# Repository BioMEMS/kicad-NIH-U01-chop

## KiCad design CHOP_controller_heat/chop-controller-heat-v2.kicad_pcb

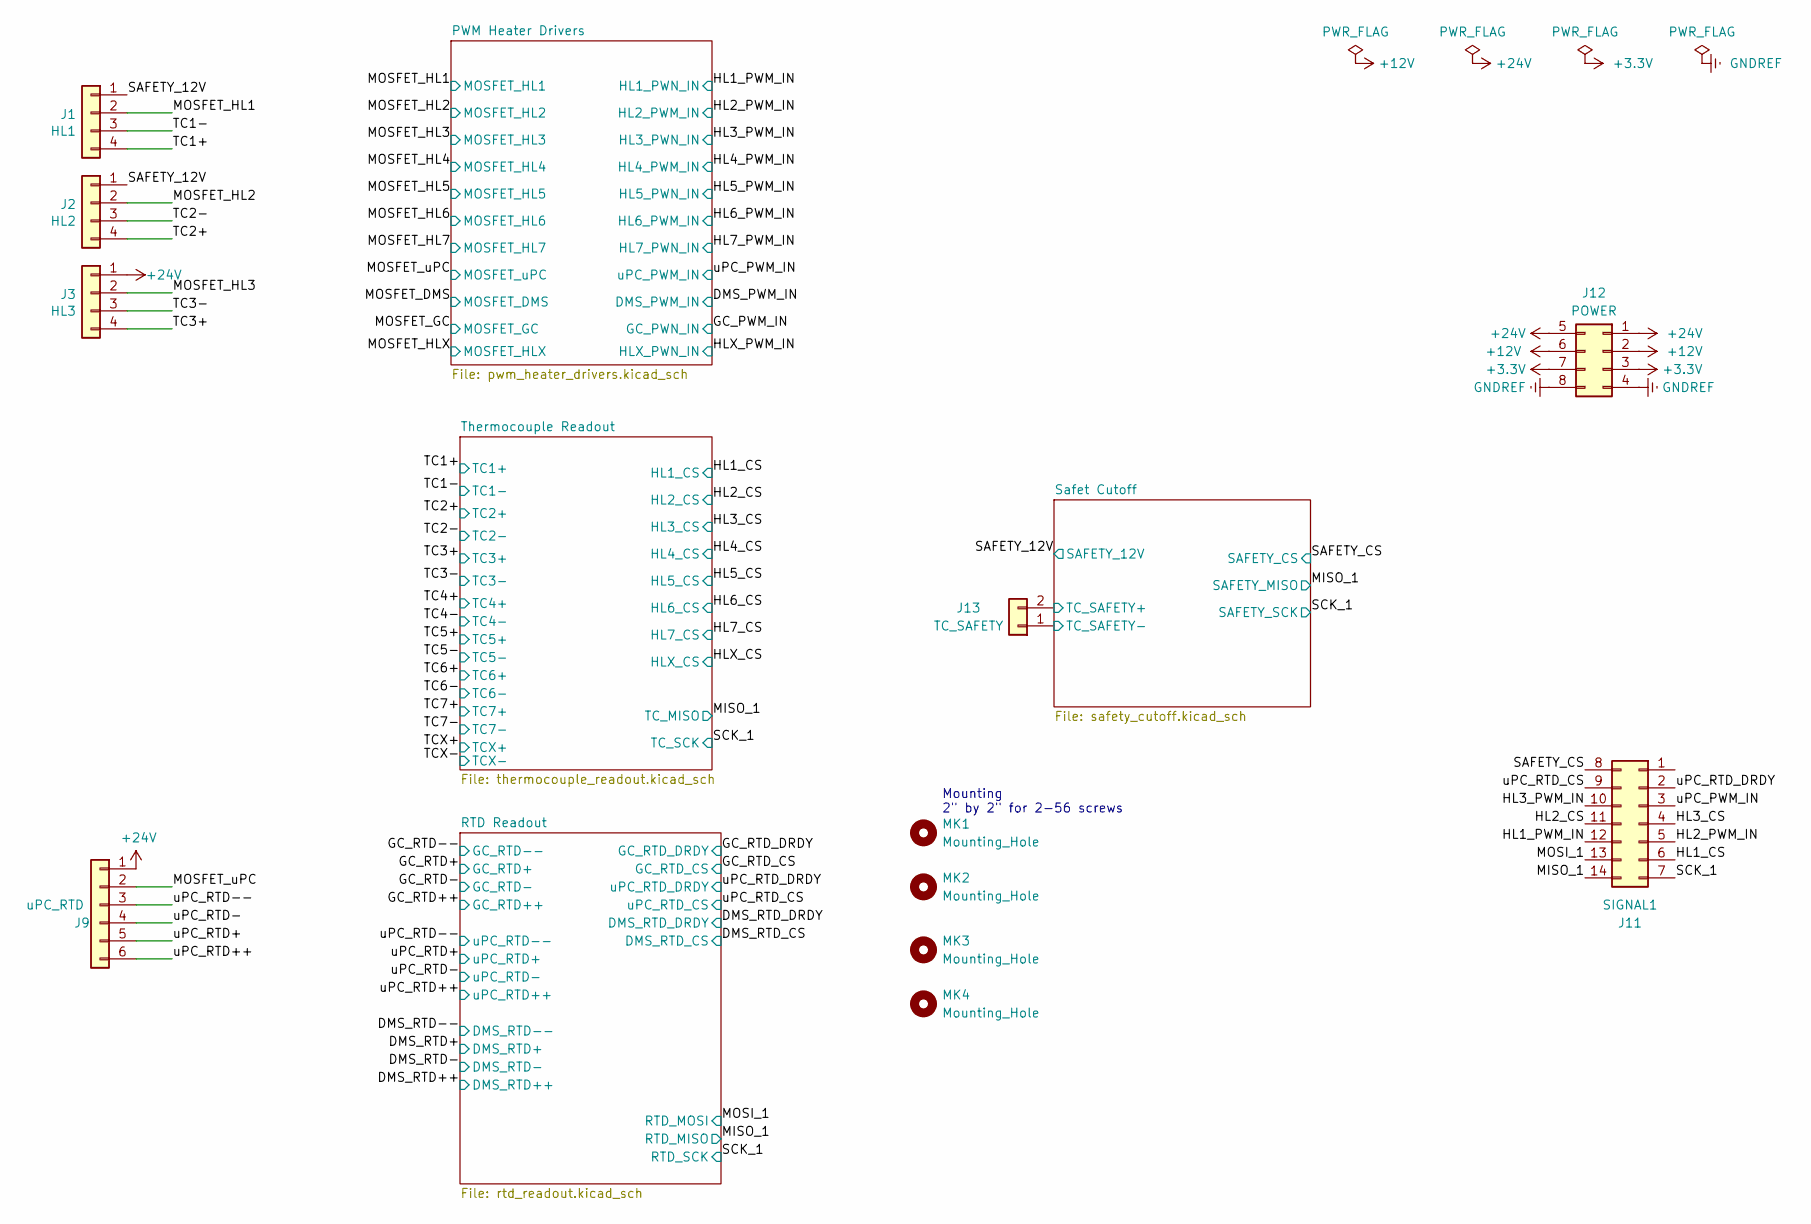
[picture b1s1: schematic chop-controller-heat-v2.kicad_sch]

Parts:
J1: HL1; Molex_SL_171975-0004_1x04_P2.54mm_Horizontal
J2: HL2; Molex_SL_171975-0004_1x04_P2.54mm_Horizontal
J3: HL3; Molex_SL_171975-0004_1x04_P2.54mm_Horizontal
J9: uPC_RTD; Molex_SL_171975-0006_1x06_P2.54mm_Horizontal
J11: SIGNAL1; Molex_Micro-Fit_3.0_43045-1400_2x07_P3.00mm_Horizontal
J12: POWER; Molex_Micro-Fit_3.0_43045-0800_2x04_P3.00mm_Horizontal
J13: TC_SAFETY; Molex_SL_171975-0002_1x02_P2.54mm_Horizontal
MK1, MK2, MK3, MK4: Mounting_Hole; MountingHole_3.2mm_M3

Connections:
+3.3V: J12.3, J12.7; also elsewhere on the board
+12V: J12.2, J12.6; also elsewhere on the board
+24V: J3.1, J9.1, J12.1, J12.5
/HL1_CS: J11.6; also elsewhere on the board
/HL1_PWM_IN: J11.12; also elsewhere on the board
/HL2_CS: J11.11; also elsewhere on the board
/HL2_PWM_IN: J11.5; also elsewhere on the board
/HL3_CS: J11.4; also elsewhere on the board
/HL3_PWM_IN: J11.10; also elsewhere on the board
/MISO_1: J11.14; also elsewhere on the board
/MOSFET_HL1: J1.2; also elsewhere on the board
/MOSFET_HL2: J2.2; also elsewhere on the board
/MOSFET_HL3: J3.2; also elsewhere on the board
/MOSFET_uPC: J9.2; also elsewhere on the board
/MOSI_1: J11.13; also elsewhere on the board
/SAFETY_12V: J1.1, J2.1; also elsewhere on the board
/SAFETY_CS: J11.8; also elsewhere on the board
/SCK_1: J11.7; also elsewhere on the board
/Safet Cutoff/TC_SAFETY+: J13.2; also elsewhere on the board
/Safet Cutoff/TC_SAFETY-: J13.1; also elsewhere on the board
/TC1+: J1.4; also elsewhere on the board
/TC1-: J1.3; also elsewhere on the board
/TC2+: J2.4; also elsewhere on the board
/TC2-: J2.3; also elsewhere on the board
/TC3+: J3.4; also elsewhere on the board
/TC3-: J3.3; also elsewhere on the board
/uPC_PWM_IN: J11.3; also elsewhere on the board
/uPC_RTD+: J9.5; also elsewhere on the board
/uPC_RTD++: J9.6; also elsewhere on the board
/uPC_RTD-: J9.4; also elsewhere on the board
/uPC_RTD--: J9.3; also elsewhere on the board
/uPC_RTD_CS: J11.9; also elsewhere on the board
/uPC_RTD_DRDY: J11.2; also elsewhere on the board
GNDREF: J12.4, J12.8; also elsewhere on the board

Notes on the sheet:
Mounting 2" by 2" for 2-56 screws

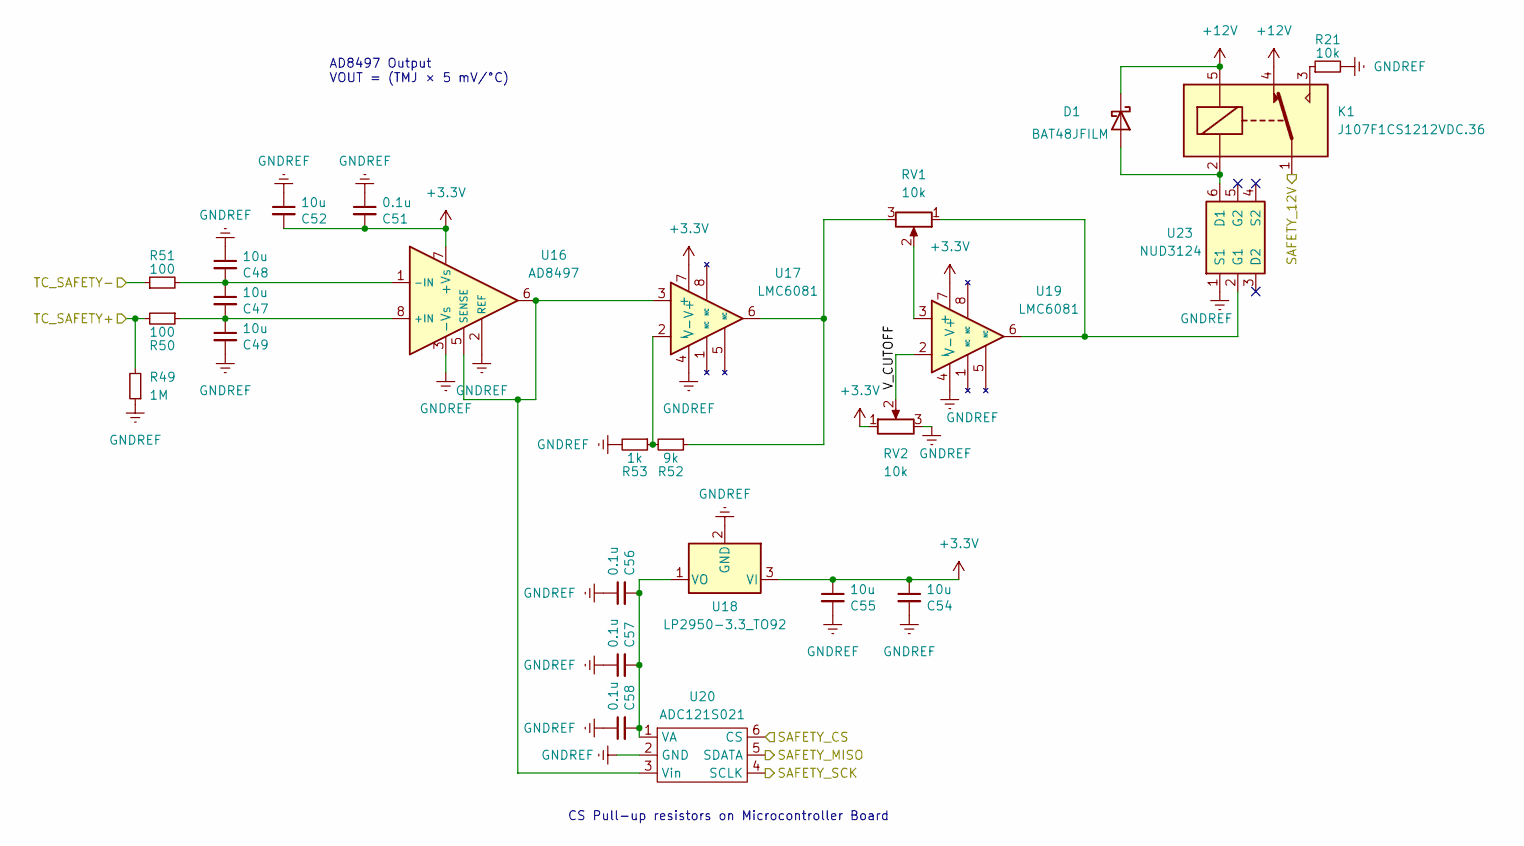
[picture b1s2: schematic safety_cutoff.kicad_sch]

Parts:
C47, C48, C49, C52, C54, C55: 10u; C_0603_1608Metric_HandSolder
C51, C56, C57, C58: 0.1u; C_0603_1608Metric_HandSolder
D1: BAT48JFILM; D_SOD-323
K1: J107F1CS1212VDC.36; Relay_SPDT_SANYOU_SRD_Series_Form_C
R21: 10k; R_0603_1608Metric
R49: 1M; R_0603_1608Metric
R50, R51: 100; R_0603_1608Metric
R52: 9k; R_0603_1608Metric
R53: 1k; R_0603_1608Metric
RV1, RV2: 10k; Potentiometer_Bourns_3296W_Vertical
U16: AD8497; MSOP-8_3x3mm_P0.65mm
U17, U19: LMC6081; SOIC-8_3.9x4.9mm_P1.27mm
U18: LP2950-3.3_TO92; TO-92_Inline
U20: ADC121S021; SOT-23-6
U23: NUD3124; SOT-23-6

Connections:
+3.3V: C51.2, C52.2, C54.1, C55.1, RV2.1, U16.7 (+Vs), U17.7 (V+), U18.3 (VI), U19.7 (V+); also elsewhere on the board
+12V: D1.1 (K), K1.4, K1.5; also elsewhere on the board
/MISO_1: U20.5 (SDATA); also elsewhere on the board
/SAFETY_12V: K1.1; also elsewhere on the board
/SAFETY_CS: U20.6 (CS); also elsewhere on the board
/SCK_1: U20.4 (SCLK); also elsewhere on the board
/Safet Cutoff/TC_SAFETY+: R49.2, R50.2; also elsewhere on the board
/Safet Cutoff/TC_SAFETY-: R51.1; also elsewhere on the board
/Safet Cutoff/V_CUTOFF: RV2.2, U19.2 (-)
GNDREF: C48.1, C49.2, C51.1, C52.1, C54.2, C55.2, C56.1, C57.1, C58.1, R21.2, R49.1, R53.2, RV2.3, U16.2 (REF), U16.3 (-Vs), U17.4 (V-), U18.2 (GND), U19.4 (V-), U20.2 (GND), U23.1 (S1); also elsewhere on the board
unnamed: D1.2 (A), K1.2, U23.6 (D1)
unnamed: K1.3, R21.1
unnamed: R52.1, RV1.3, U17.6
unnamed: C47.2, C49.1, R50.1, U16.8 (+IN)
unnamed: C47.1, C48.2, R51.2, U16.1 (-IN)
unnamed: U16.5 (SENSE), U16.6, U17.3 (+), U20.3 (Vin)
unnamed: R52.2, R53.1, U17.2 (-)
unnamed: C56.2, C57.2, C58.2, U18.1 (VO), U20.1 (VA)
unnamed: RV1.2, U19.3 (+)
unnamed: RV1.1, U19.6, U23.2 (G1)

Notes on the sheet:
AD8497 Output VOUT = (TMJ × 5 mV/°C)
CS Pull-up resistors on Microcontroller Board

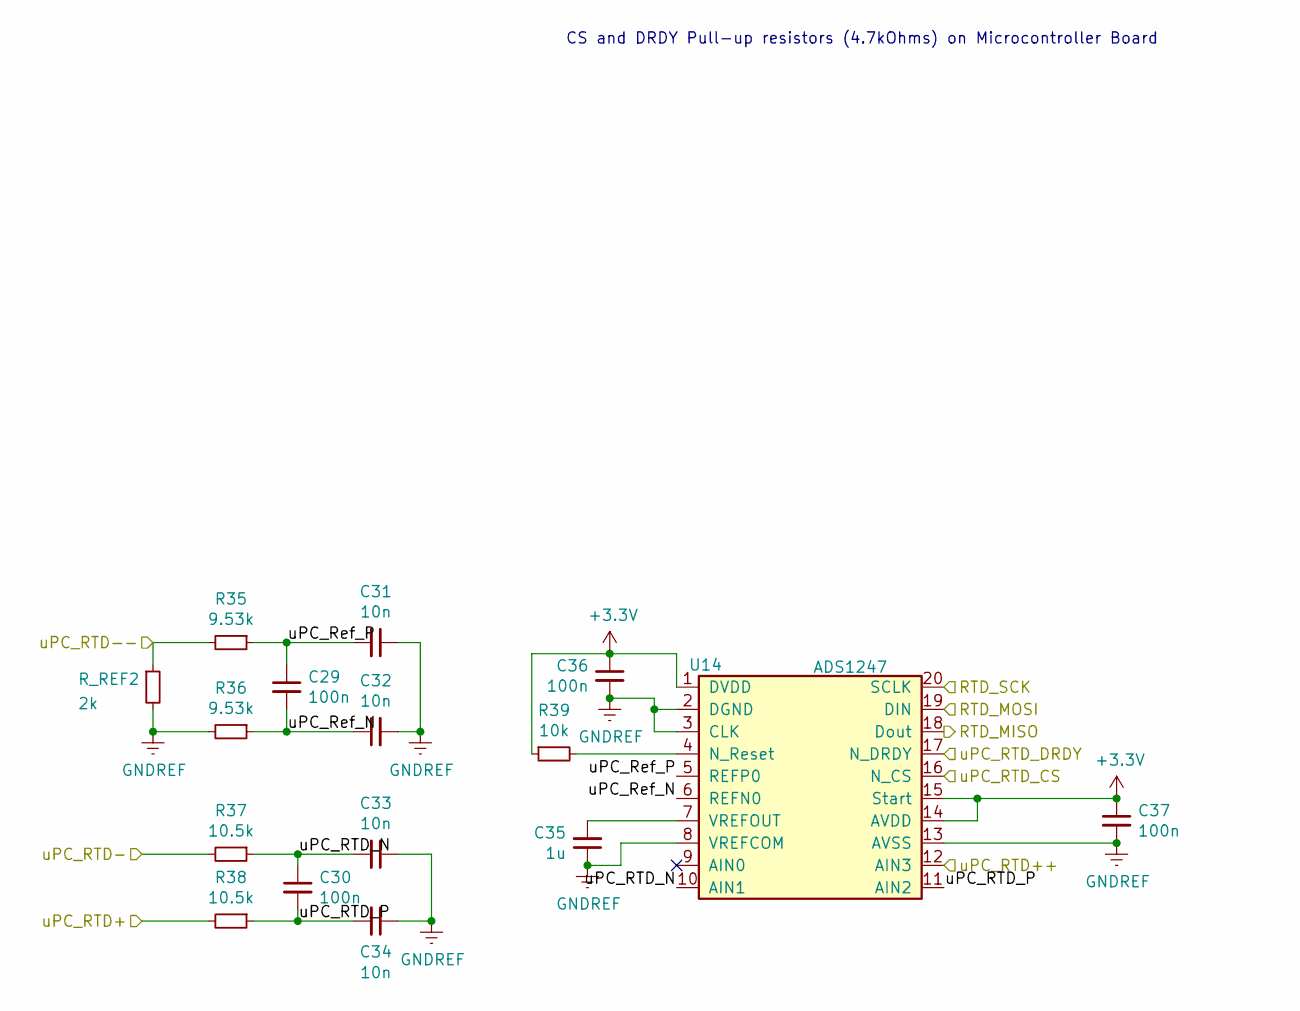
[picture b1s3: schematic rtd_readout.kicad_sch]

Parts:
C29, C30, C36, C37: 100n; C_0603_1608Metric_HandSolder
C31, C32, C33, C34: 10n; C_0603_1608Metric_HandSolder
C35: 1u; C_0603_1608Metric_HandSolder
R35, R36: 9.53k; R_0603_1608Metric
R37, R38: 10.5k; R_0603_1608Metric
R39: 10k; R_0603_1608Metric
R_REF2: 2k; R_0603_1608Metric
U14: ADS1247; TSSOP-20_4.4x6.5mm_P0.65mm; MPN ADS1247IPW

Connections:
+3.3V: C36.1, C37.1, R39.1, U14.1 (DVDD), U14.14 (AVDD), U14.15 (Start); also elsewhere on the board
/MISO_1: U14.18 (Dout); also elsewhere on the board
/MOSI_1: U14.19 (DIN); also elsewhere on the board
/RTD Readout/uPC_RTD_N: C30.1, C33.2, R37.1, U14.10 (AIN1)
/RTD Readout/uPC_RTD_P: C30.2, C34.2, R38.1, U14.11 (AIN2)
/RTD Readout/uPC_Ref_N: C29.2, C32.1, R36.1, U14.6 (REFN0)
/RTD Readout/uPC_Ref_P: C29.1, C31.2, R35.1, U14.5 (REFP0)
/SCK_1: U14.20 (SCLK); also elsewhere on the board
/uPC_RTD+: R38.2; also elsewhere on the board
/uPC_RTD++: U14.12 (AIN3); also elsewhere on the board
/uPC_RTD-: R37.2; also elsewhere on the board
/uPC_RTD--: R35.2, R_REF2.1; also elsewhere on the board
/uPC_RTD_CS: U14.16 (N_CS); also elsewhere on the board
/uPC_RTD_DRDY: U14.17 (N_DRDY); also elsewhere on the board
GNDREF: C31.1, C32.2, C33.1, C34.1, C35.1, C36.2, C37.2, R36.2, R_REF2.2, U14.2 (DGND), U14.3 (CLK), U14.8 (VREFCOM), U14.13 (AVSS); also elsewhere on the board
unnamed: R39.2, U14.4 (N_Reset)
unnamed: C35.2, U14.7 (VREFOUT)

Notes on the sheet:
CS and DRDY Pull-up resistors (4.7kOhms) on Microcontroller Board

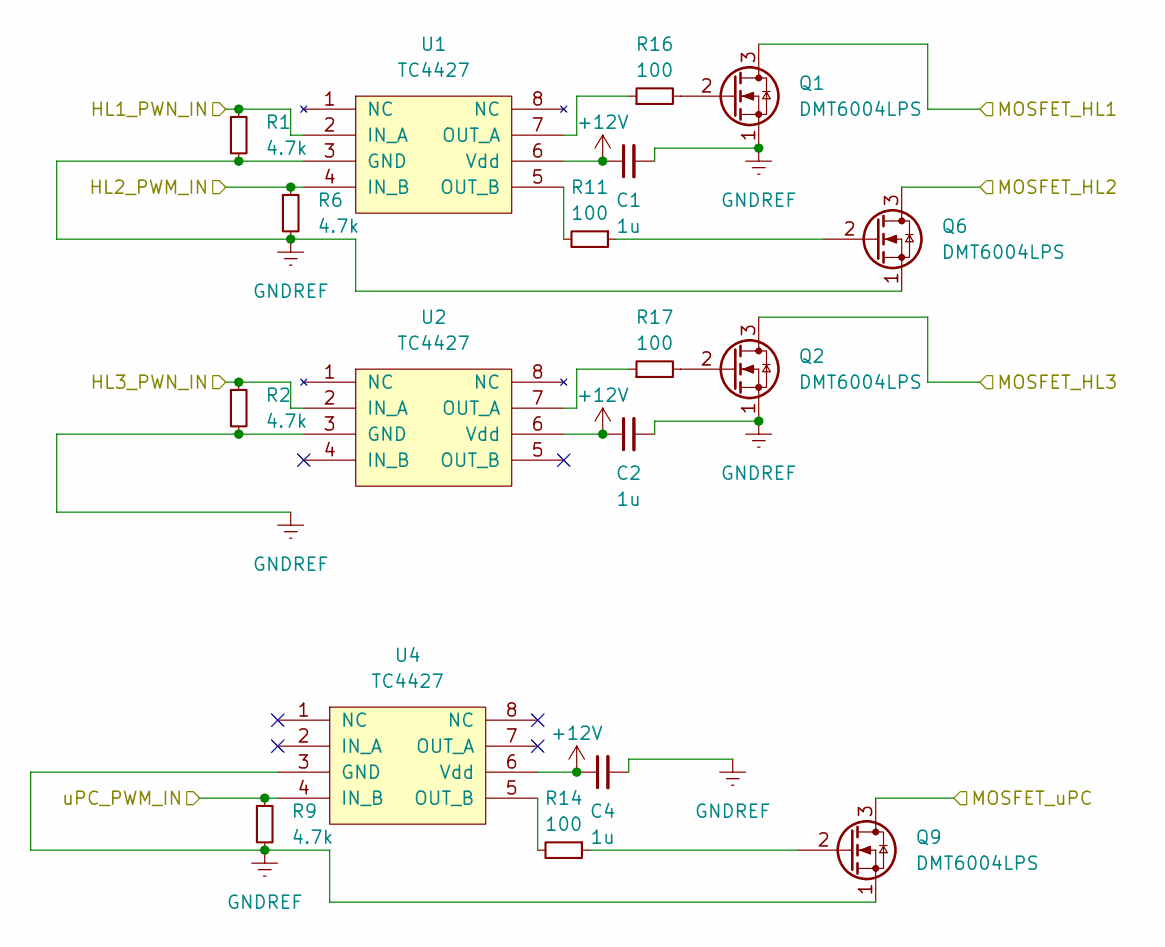
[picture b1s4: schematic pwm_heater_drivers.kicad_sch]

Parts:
C1, C2, C4: 1u; C_0603_1608Metric_HandSolder
Q1, Q2, Q6, Q9: DMT6004LPS; PowerDI5060-8
R1, R2, R6, R9: 4.7k; R_0603_1608Metric
R11, R14, R16, R17: 100; R_0603_1608Metric
U1, U2, U4: TC4427; MSOP-8_3x3mm_P0.65mm_TI

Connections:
+12V: C1.1, C2.1, C4.1, U1.6 (Vdd), U2.6 (Vdd), U4.6 (Vdd); also elsewhere on the board
/HL1_PWM_IN: R1.1, U1.2 (IN_A); also elsewhere on the board
/HL2_PWM_IN: R6.1, U1.4 (IN_B); also elsewhere on the board
/HL3_PWM_IN: R2.1, U2.2 (IN_A); also elsewhere on the board
/MOSFET_HL1: Q1.3 (D); also elsewhere on the board
/MOSFET_HL2: Q6.3 (D); also elsewhere on the board
/MOSFET_HL3: Q2.3 (D); also elsewhere on the board
/MOSFET_uPC: Q9.3 (D); also elsewhere on the board
/uPC_PWM_IN: R9.1, U4.4 (IN_B); also elsewhere on the board
GNDREF: C1.2, C2.2, C4.2, Q1.1 (S), Q2.1 (S), Q6.1 (S), Q9.1 (S), R1.2, R2.2, R6.2, R9.2, U1.3 (GND), U2.3 (GND), U4.3 (GND); also elsewhere on the board
unnamed: Q1.2 (G), R16.2
unnamed: Q2.2 (G), R17.2
unnamed: Q6.2 (G), R11.1
unnamed: Q9.2 (G), R14.1
unnamed: R16.1, U1.7 (OUT_A)
unnamed: R11.2, U1.5 (OUT_B)
unnamed: R17.1, U2.7 (OUT_A)
unnamed: R14.2, U4.5 (OUT_B)

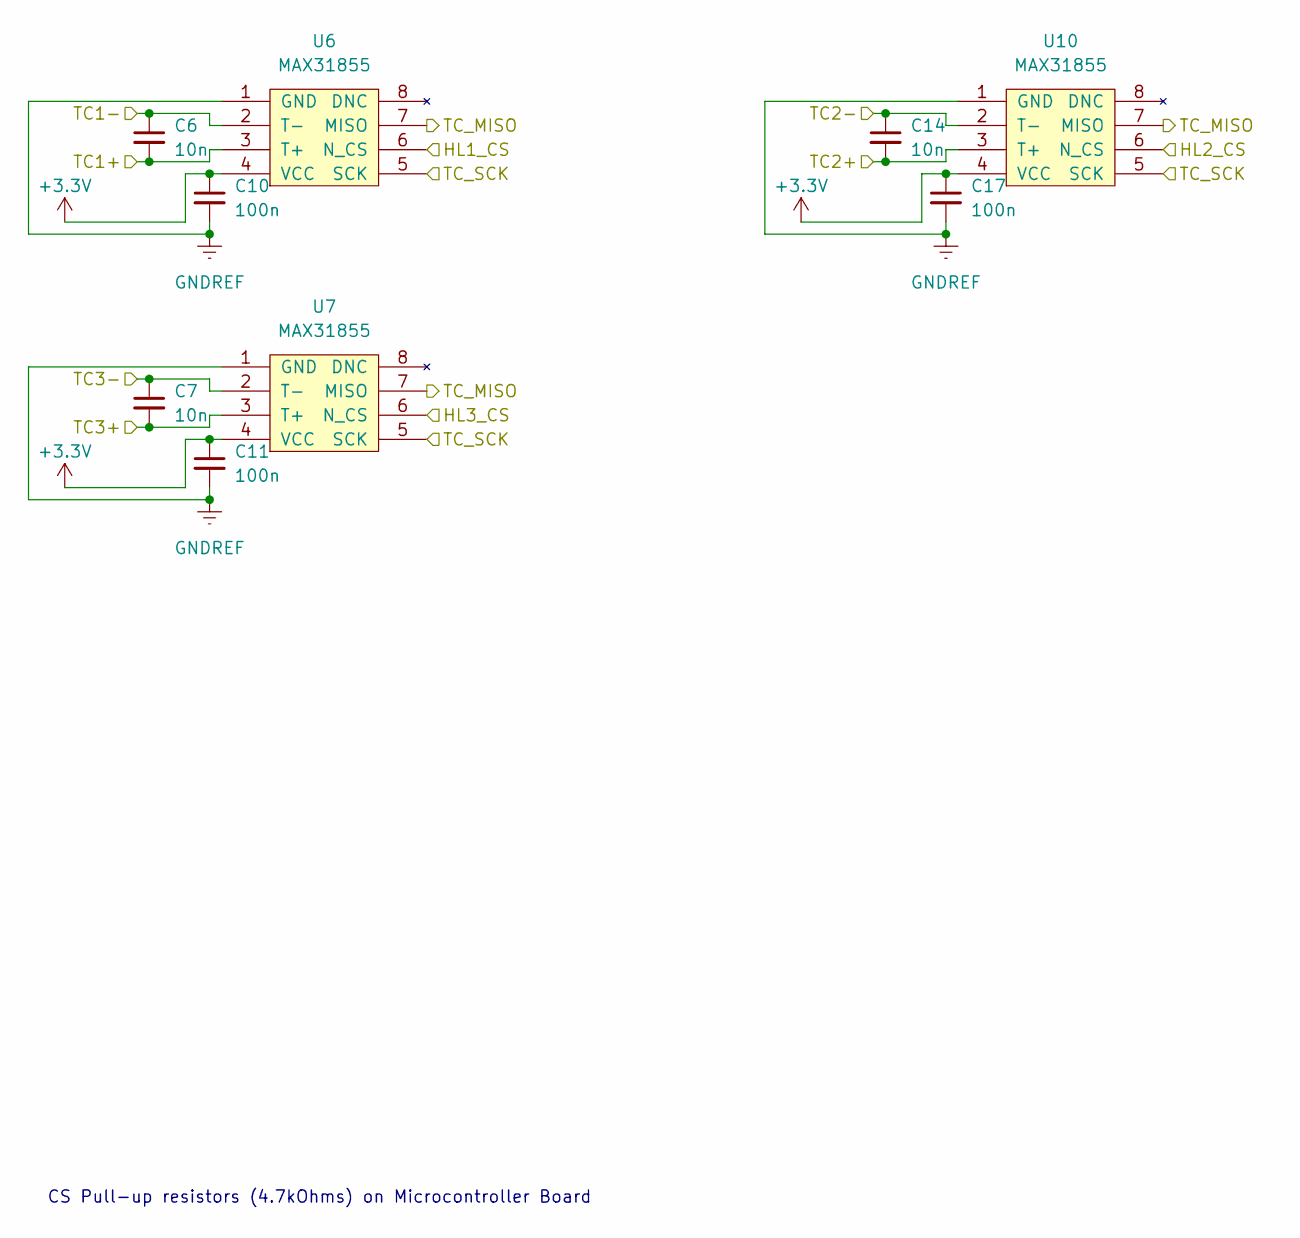
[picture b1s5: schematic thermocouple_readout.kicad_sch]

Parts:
C6, C7, C14: 10n; C_0603_1608Metric_HandSolder
C10, C11, C17: 100n; C_0603_1608Metric_HandSolder
U6, U7, U10: MAX31855; SO-8_Maxim

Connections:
+3.3V: C10.1, C11.1, C17.1, U6.4 (VCC), U7.4 (VCC), U10.4 (VCC); also elsewhere on the board
/HL1_CS: U6.6 (N_CS); also elsewhere on the board
/HL2_CS: U10.6 (N_CS); also elsewhere on the board
/HL3_CS: U7.6 (N_CS); also elsewhere on the board
/MISO_1: U6.7 (MISO), U7.7 (MISO), U10.7 (MISO); also elsewhere on the board
/SCK_1: U6.5 (SCK), U7.5 (SCK), U10.5 (SCK); also elsewhere on the board
/TC1+: C6.2, U6.3 (T+); also elsewhere on the board
/TC1-: C6.1, U6.2 (T-); also elsewhere on the board
/TC2+: C14.2, U10.3 (T+); also elsewhere on the board
/TC2-: C14.1, U10.2 (T-); also elsewhere on the board
/TC3+: C7.2, U7.3 (T+); also elsewhere on the board
/TC3-: C7.1, U7.2 (T-); also elsewhere on the board
GNDREF: C10.2, C11.2, C17.2, U6.1 (GND), U7.1 (GND), U10.1 (GND); also elsewhere on the board

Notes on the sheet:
CS Pull-up resistors (4.7kOhms) on Microcontroller Board

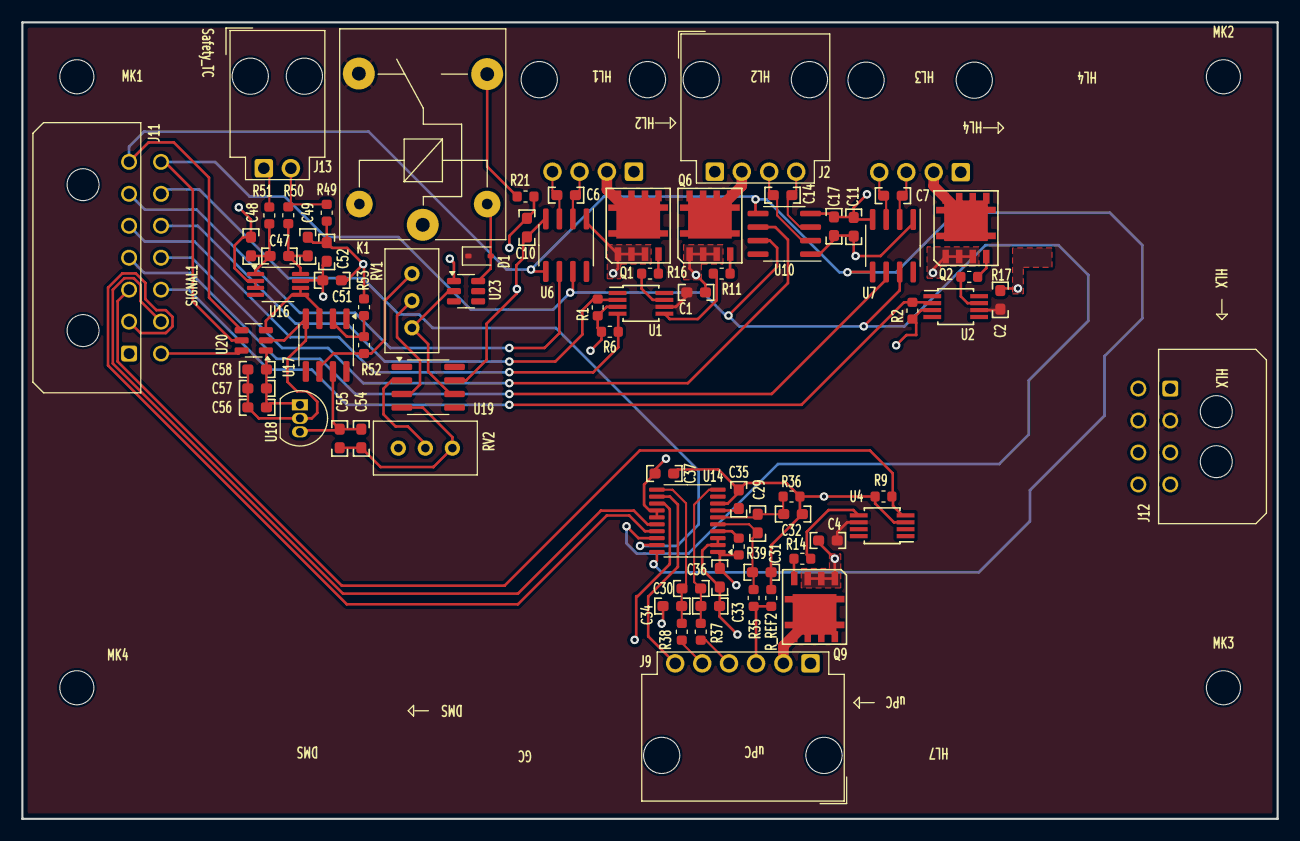
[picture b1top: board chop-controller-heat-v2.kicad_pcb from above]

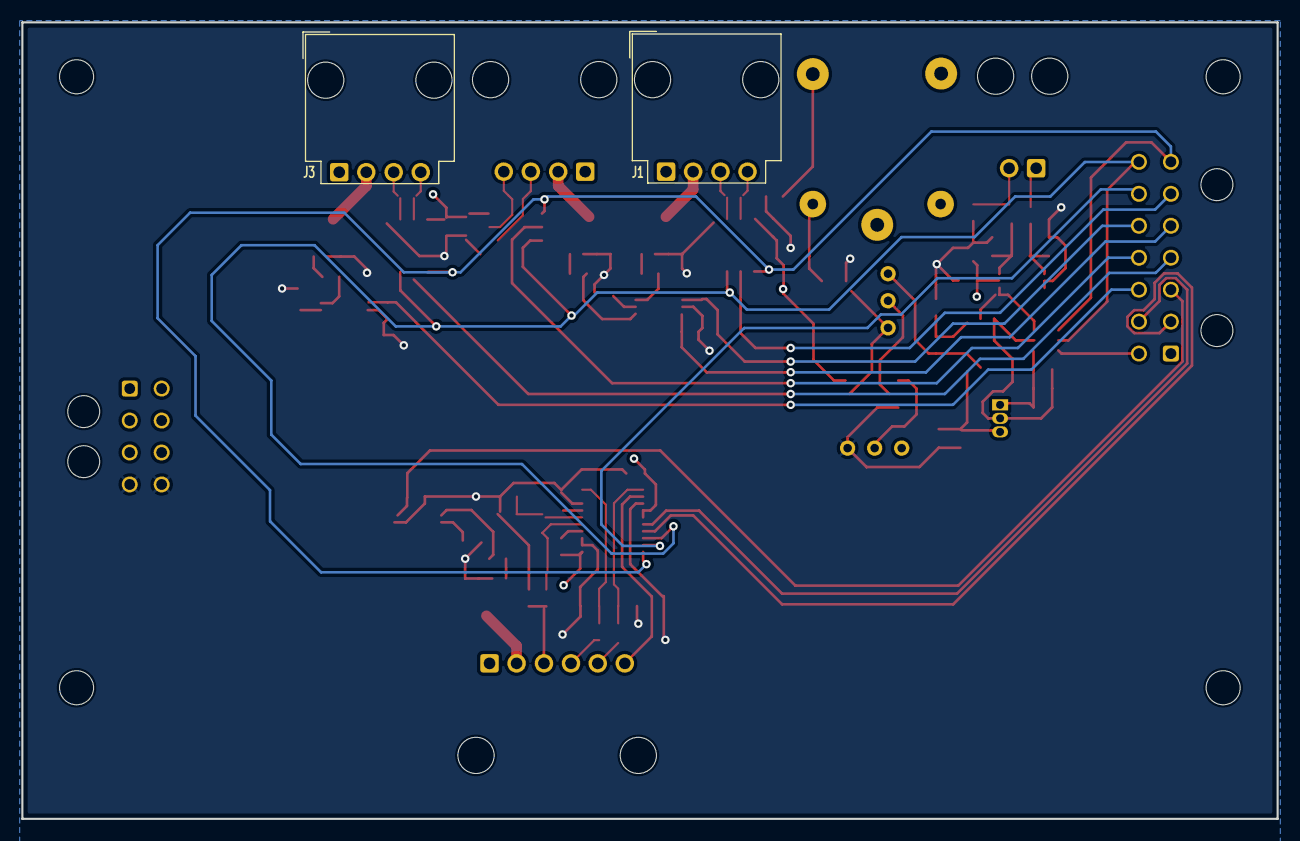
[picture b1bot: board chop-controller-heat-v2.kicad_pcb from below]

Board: 4 copper layers, 117.9 x 74.8 mm, 80 parts (2 on the bottom side), 59 nets.

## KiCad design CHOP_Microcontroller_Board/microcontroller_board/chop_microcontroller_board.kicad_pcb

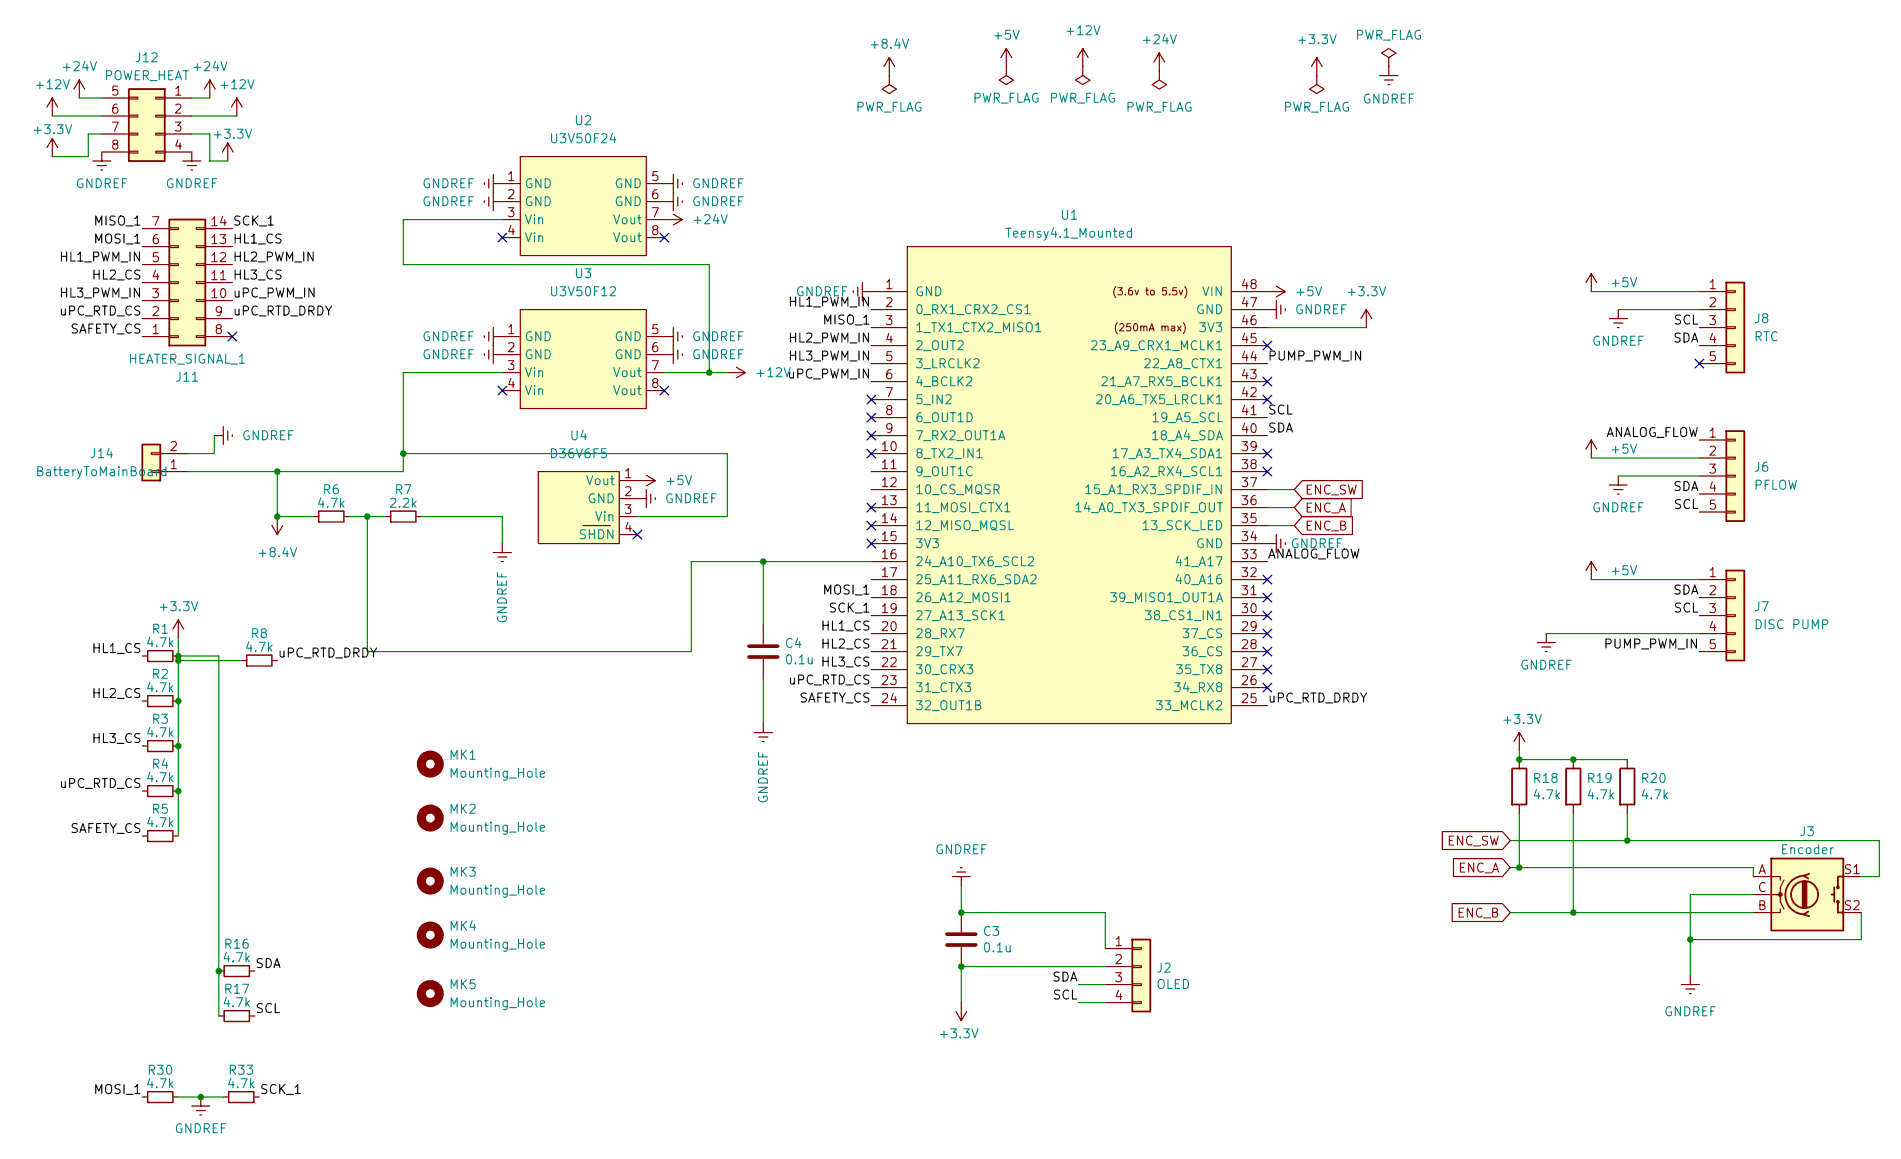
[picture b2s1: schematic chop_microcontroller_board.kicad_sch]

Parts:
C3, C4: 0.1u; C_0603_1608Metric_HandSolder
J2: OLED; 128x64OLED
J3: Encoder; RotaryEncoder_Alps_EC12E-Switch_Vertical_H20mm
J6: PFLOW; Molex_Micro-Fit_3.0_43650-0500_1x05_P3.00mm_Horizontal
J7: DISC PUMP; Molex_Micro-Fit_3.0_43650-0500_1x05_P3.00mm_Horizontal
J8: RTC; PinHeader_1x05_P2.54mm_Vertical
J11: HEATER_SIGNAL_1; Molex_Micro-Fit_3.0_43045-1400_2x07_P3.00mm_Horizontal
J12: POWER_HEAT; Molex_Micro-Fit_3.0_43045-0800_2x04_P3.00mm_Horizontal
J14: BatteryToMainBoard; JST_PH_S2B-PH-K_1x02_P2.00mm_Horizontal
MK1, MK2, MK3, MK4, MK5: Mounting_Hole; MountingHole_3.2mm_M3
R1, R2, R3, R4, R5, R6, R8, R16, R17, R30, R33: 4.7k; R_0603_1608Metric
R7: 2.2k; R_0603_1608Metric
R18, R19, R20: 4.7k; R_0805_2012Metric
U1: Teensy4.1_Mounted; Teensy41_Mounted
U2: U3V50F24; U3V50F24StepUpReg
U3: U3V50F12; U3V50F12StepUpReg
U4: D36V6F5; PinHeader_1x04_P2.54mm_Vertical

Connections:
+3.3V: C3.2, J2.2, J12.3, J12.7, R1.2, R2.2, R3.2, R4.2, R5.2, R8.1, R16.2, R17.2, R18.1, R19.1, R20.1, U1.46 (3V3)
+5V: J6.2, J7.1, J8.1, U1.48 (VIN), U4.1 (Vout)
+8.4V: J14.1, R6.1, U3.3 (Vin), U4.3 (Vin)
+12V: J12.2, J12.6, U2.3 (Vin), U3.7 (Vout)
+24V: J12.1, J12.5, U2.7 (Vout)
/ANALOG_FLOW: J6.1, U1.33 (41_A17)
/HL1_CS: J11.13, R1.1, U1.20 (28_RX7)
/HL1_PWM_IN: J11.5, U1.2 (0_RX1_CRX2_CS1)
/HL2_CS: J11.4, R2.1, U1.21 (29_TX7)
/HL2_PWM_IN: J11.12, U1.4 (2_OUT2)
/HL3_CS: J11.11, R3.1, U1.22 (30_CRX3)
/HL3_PWM_IN: J11.3, U1.5 (3_LRCLK2)
/MISO_1: J11.7, U1.3 (1_TX1_CTX2_MISO1)
/MOSI_1: J11.6, R30.1, U1.18 (26_A12_MOSI1)
/PUMP_PWM_IN: J7.5, U1.44 (22_A8_CTX1)
/SAFETY_CS: J11.1, R5.1, U1.24 (32_OUT1B)
/SCK_1: J11.14, R33.1, U1.19 (27_A13_SCK1)
/SCL: J2.4, J6.5, J7.3, J8.3, R17.1, U1.41 (19_A5_SCL)
/SDA: J2.3, J6.4, J7.2, J8.4, R16.1, U1.40 (18_A4_SDA)
/uPC_PWM_IN: J11.10, U1.6 (4_BCLK2)
/uPC_RTD_CS: J11.2, R4.1, U1.23 (31_CTX3)
/uPC_RTD_DRDY: J11.9, R8.2, U1.25 (33_MCLK2)
ENC_A: J3.A, R18.2, U1.36 (14_A0_TX3_SPDIF_OUT)
ENC_B: J3.B, R19.2, U1.35 (13_SCK_LED)
ENC_SW: J3.S1, R20.2, U1.37 (15_A1_RX3_SPDIF_IN)
GNDREF: C3.1, C4.2, J2.1, J3.C, J3.S2, J6.3, J7.4, J8.2, J12.4, J12.8, J14.2, R7.2, R30.2, R33.2, U1.1 (GND), U1.34 (GND), U1.47 (GND), U2.1 (GND), U2.2 (GND), U2.5 (GND), U2.6 (GND), U3.1 (GND), U3.2 (GND), U3.5 (GND), U3.6 (GND), U4.2 (GND)
unnamed: C4.1, R6.2, R7.1, U1.16 (24_A10_TX6_SCL2)

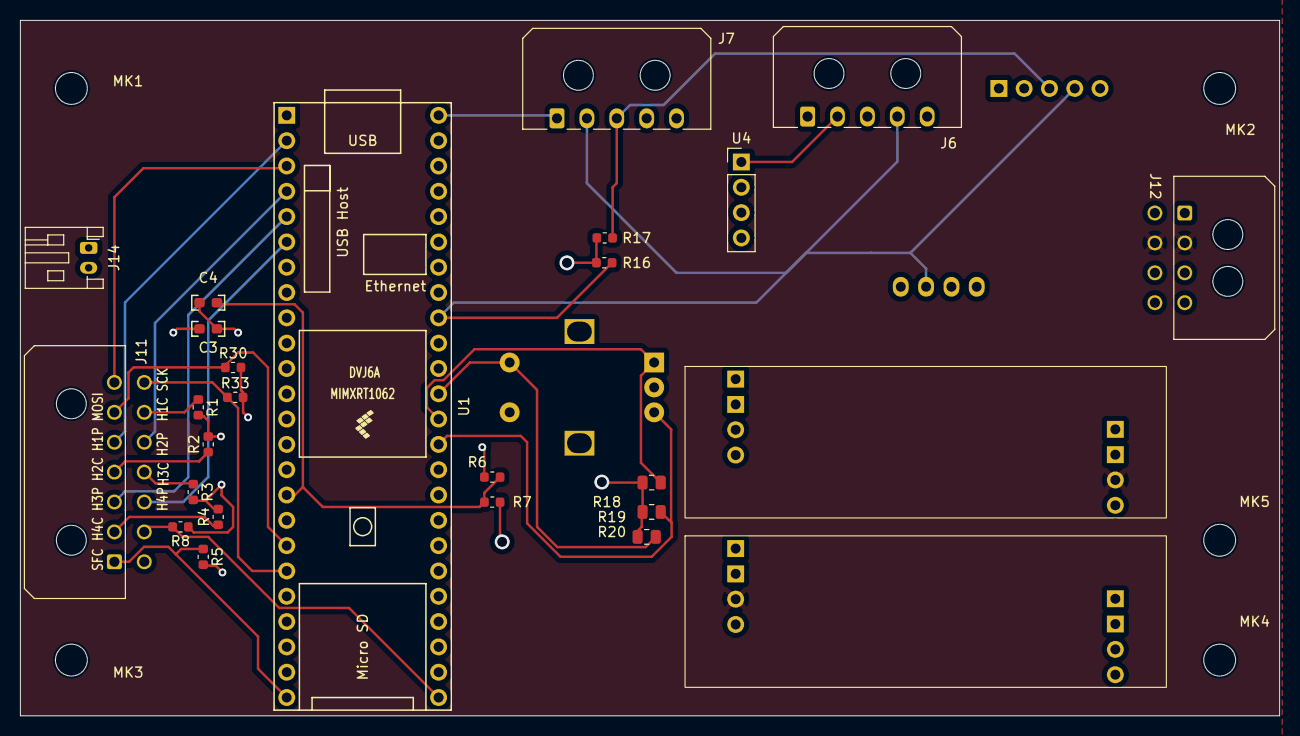
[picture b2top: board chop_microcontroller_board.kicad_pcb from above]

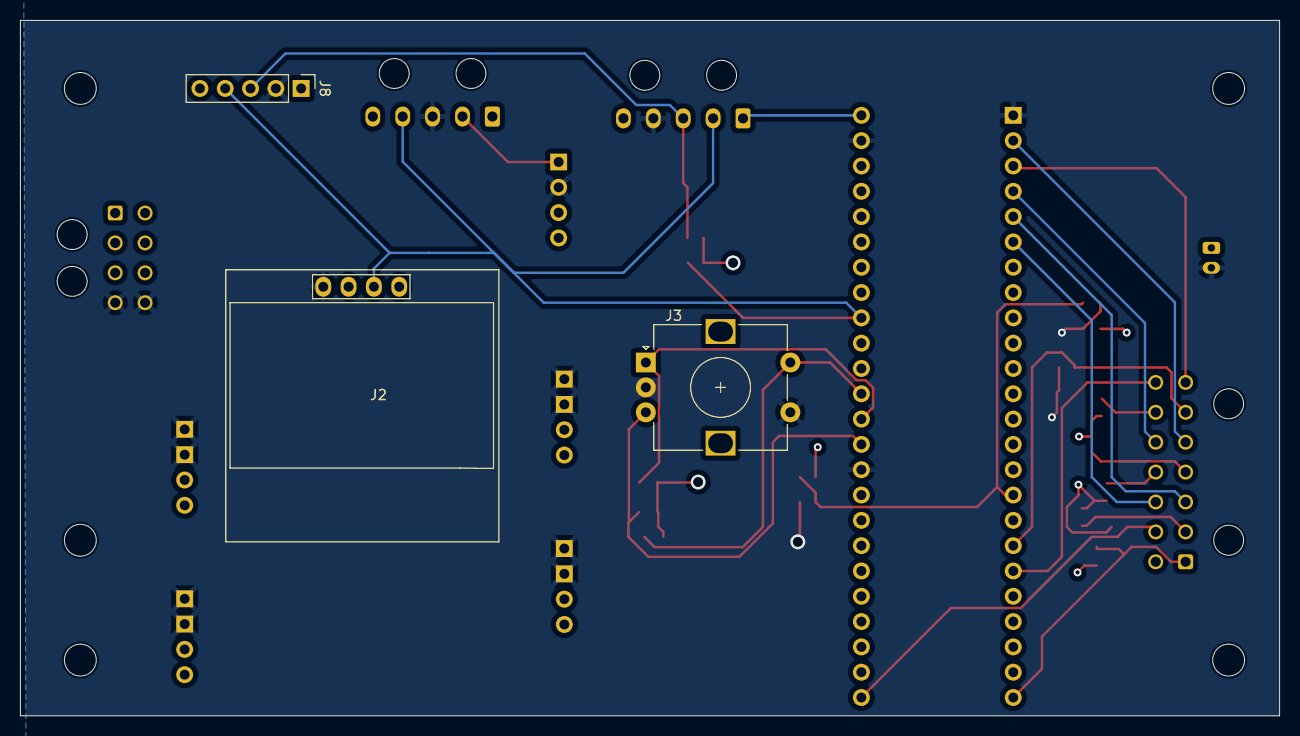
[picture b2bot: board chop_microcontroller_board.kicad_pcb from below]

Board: 4 copper layers, 126.4 x 69.8 mm, 34 parts (3 on the bottom side), 27 nets.

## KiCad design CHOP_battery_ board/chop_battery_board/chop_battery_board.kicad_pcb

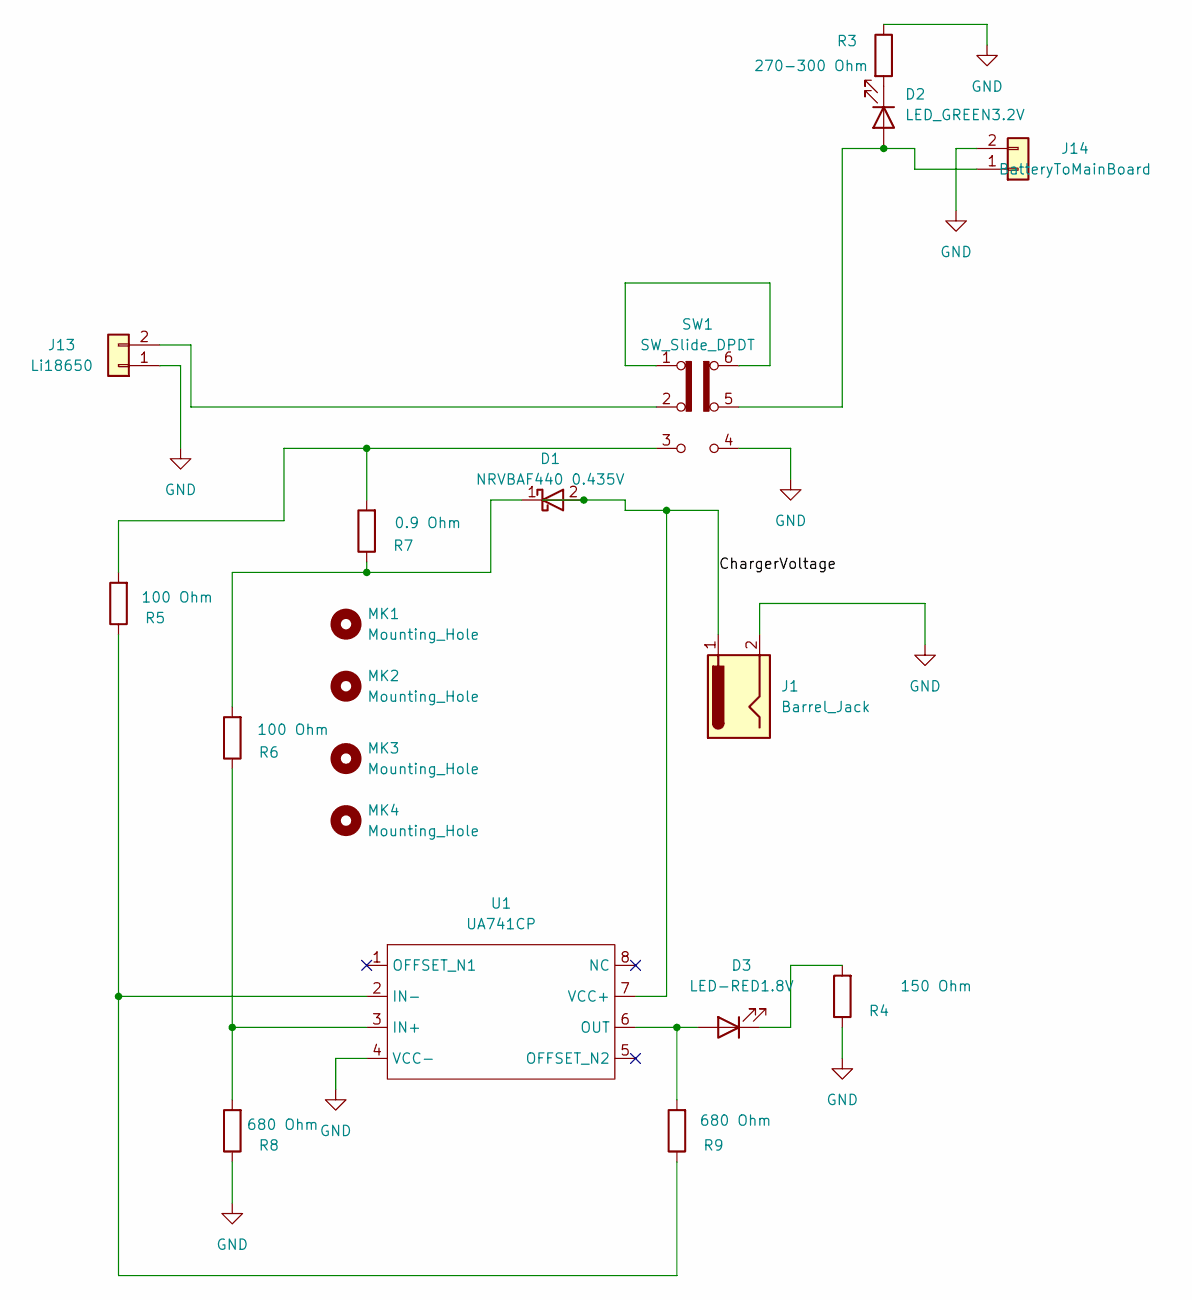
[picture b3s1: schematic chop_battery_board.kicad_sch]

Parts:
D1: NRVBAF440 0.435V; D_SMA
D2: LED_GREEN3.2V; LED_0603_1608Metric
D3: LED-RED1.8V; LED_0603_1608Metric
J1: Barrel_Jack; BarrelJack_CUI_PJ-102AH_Horizontal
J13: Li18650; JST_PH_S2B-PH-K_1x02_P2.00mm_Horizontal
J14: BatteryToMainBoard; JST_EH_S2B-EH_1x02_P2.50mm_Horizontal
MK1, MK2, MK3, MK4: Mounting_Hole; MountingHole_3.2mm_M3
R3: 270-300 Ohm; R_0603_1608Metric
R4: 150 Ohm; R_0603_1608Metric
R5, R6: 100 Ohm; R_0603_1608Metric
R7: 0.9 Ohm; R_0603_1608Metric
R8, R9: 680 Ohm; R_0603_1608Metric
SW1: SW_Slide_DPDT; Relay_DPDT_Omron_G6A
U1: UA741CP; SOIC-8-1EP_3.9x4.9mm_P1.27mm_EP2.95x4.9mm_Mask2.71x3.4mm

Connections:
/ChargerVoltage: D1.2, J1.1, U1.7 (VCC+)
GND: J1.2, J13.1, J14.2, R3.1, R4.1, R8.1, SW1.4 (A), U1.4 (VCC-)
unnamed: D1.1, R6.2, R7.1
unnamed: D2.2 (A), J14.1, SW1.5 (B)
unnamed: D2.1 (K), R3.2
unnamed: D3.2 (A), R9.2, U1.6 (OUT)
unnamed: D3.1 (K), R4.2
unnamed: J13.2, SW1.2 (B)
unnamed: R5.2, R7.2, SW1.3 (C)
unnamed: SW1.1 (A), SW1.6 (C)
unnamed: R6.1, R8.2, U1.3 (IN+)
unnamed: R5.1, R9.1, U1.2 (IN-)
